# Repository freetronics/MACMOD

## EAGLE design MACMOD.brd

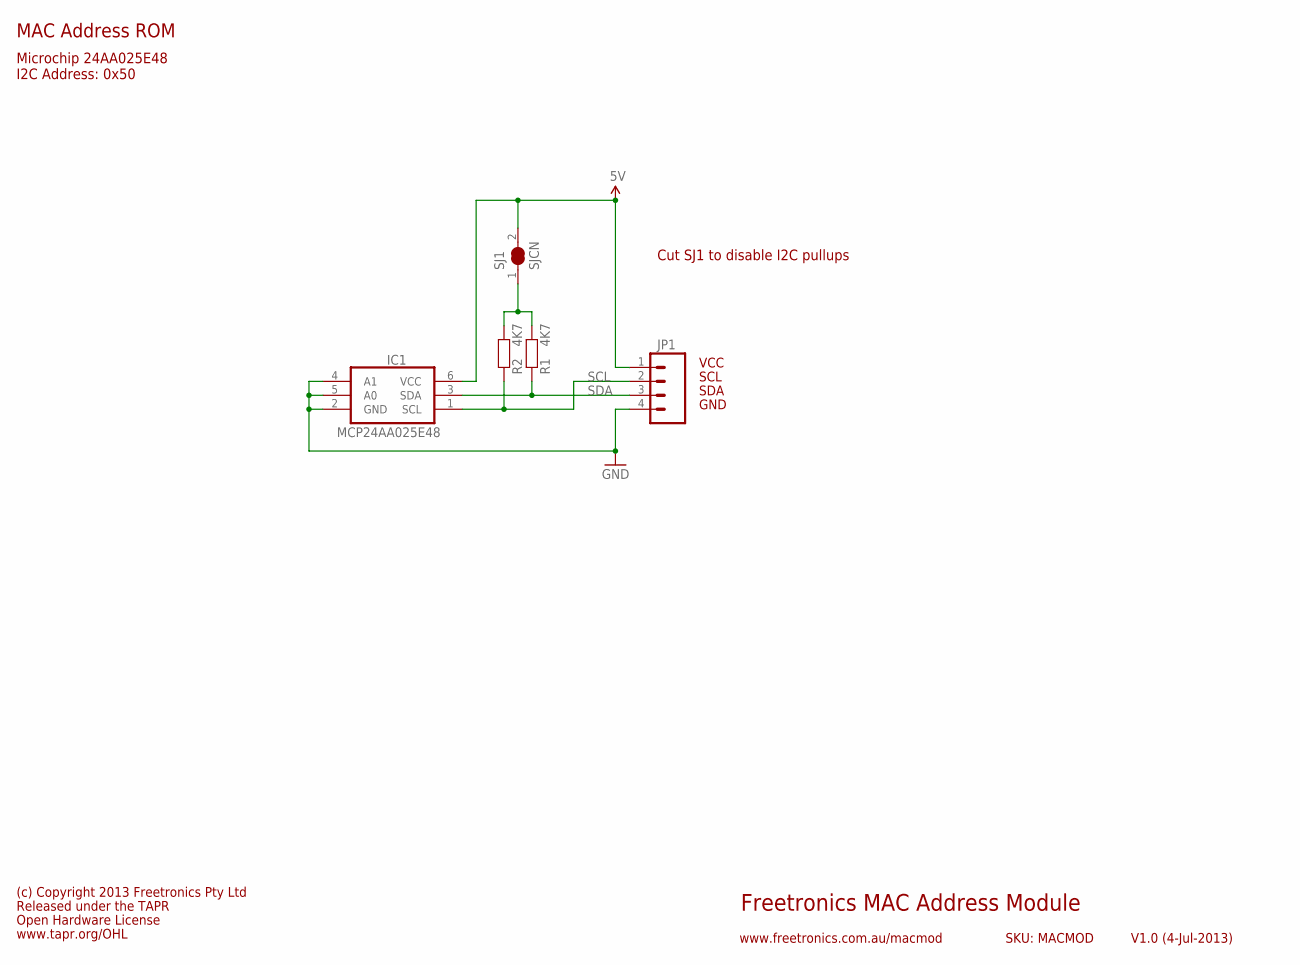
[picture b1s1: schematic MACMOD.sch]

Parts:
IC1: MCP24AA025E48; SOT23-6
JP1: M04PTH; 1X04
R1, R2: 4K7; 0603
SJ1: SJCN; SJC

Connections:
5V: IC1.6 (VCC), JP1.1, SJ1.2
GND: IC1.2 (GND), IC1.4 (A1), IC1.5 (A0), JP1.4
unnamed: R1.2, R2.2, SJ1.1
SCL: IC1.1 (SCL), JP1.2, R2.1
SDA: IC1.3 (SDA), JP1.3, R1.1

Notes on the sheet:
Freetronics MAC Address Module
V1.0 (4-Jul-2013)
www.freetronics.com.au/macmod
SKU: MACMOD
Microchip 24AA025E48 I2C Address: 0x50
MAC Address ROM
Released under the TAPR
Open Hardware License
www.tapr.org/OHL
(c) Copyright 2013 Freetronics Pty Ltd
VCC
SCL
SDA
GND
Cut SJ1 to disable I2C pullups

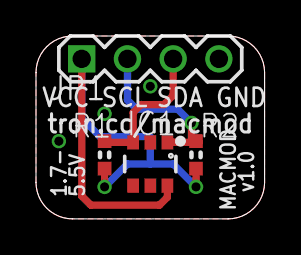
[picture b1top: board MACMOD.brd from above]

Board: 2 copper layers, 12.7 x 10.2 mm, 5 parts (1 on the bottom side), 5 nets.

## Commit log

2017-08-01 Initial project import
2017-08-01 Improved labels for v1.0 release
2017-08-04 Improved silkscreen for v1.0 release

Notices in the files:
parts and their libraries:
freetronics-original: Licensing: CC v3.0 Share-Alike You are welcome to use this library for commercial purposes.
